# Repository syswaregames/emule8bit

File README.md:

# emule8bit
Emule - NES Emulator, 8-bit architecture, 6500 processor 
Optimized for MACOSX

8-bits
Binary: 11111111 (FF)

The only requirement is having X11 installed. X11 is no longer included in macOS, but X11 server and client libraries are available from the XQuartz project (see https://support.apple.com/en-us/HT201341).

You can download X11 from https://www.xquartz.org/ and easily install it. Typical installation path is /usr/X11 and it contains includes and libraries for X11 and OpenGL.

16kb Chunks = ROM -> Cpu maps reads

PPU

 -> Patern Memory "CHR ROM" 8kb 0x0000 - 0x1FFF (Sprites)
   -> Name Table Memory "VRAM" 2kb 0x2000 - 0x3EFF (Layout of Background)
    -> Palett Memory 0xF00 - 0x3FFF (decide which colors are displayed on the screen )

  Tile is 8 * 8 bitmap, 2 bits per pixel, (16bytes) four colors per pixel

    // Characters on NES
	// ~~~~~~~~~~~~~~~~~
	// The NES stores characters using 2-bit pixels. These are not stored sequentially
	// but in singular bit planes. For example:
	//
 	// 2-Bit Pixels       LSB Bit Plane     MSB Bit Plane
	// 0 0 0 0 0 0 0 0	  0 0 0 0 0 0 0 0   0 0 0 0 0 0 0 0
	// 0 1 1 0 0 1 1 0	  0 1 1 0 0 1 1 0   0 0 0 0 0 0 0 0
	// 0 1 2 0 0 2 1 0	  0 1 1 0 0 1 1 0   0 0 1 0 0 1 0 0
	// 0 0 0 0 0 0 0 0 =  0 0 0 0 0 0 0 0 + 0 0 0 0 0 0 0 0
	// 0 1 1 0 0 1 1 0	  0 1 1 0 0 1 1 0   0 0 0 0 0 0 0 0
	// 0 0 1 1 1 1 0 0	  0 0 1 1 1 1 0 0   0 0 0 0 0 0 0 0
	// 0 0 0 2 2 0 0 0	  0 0 0 1 1 0 0 0   0 0 0 1 1 0 0 0
	// 0 0 0 0 0 0 0 0	  0 0 0 0 0 0 0 0   0 0 0 0 0 0 0 0
	//
	// The planes are stored as 8 bytes of LSB, followed by 8 bytes of MSB

PPU - Palett

The NES PPU uses a background palette with up to 13 of these colors at a time, consisting of one common backdrop color and four subpalettes of three colors, chosen from the above set. The PPU's video memory layout allows choosing one subpalette for each 16×16 pixel area of the background. (A special video mode of the MMC5 mapper overrides this, assigning a subpalette to each 8×8-pixel tile.) Sprites have an additional set of four 3-color subpalettes (with color 0 being transparent in each) and every 8x8 or 8x16 pixels can have their own subpalette, allowing for a total of 12 different colors to use for sprites at any given time, or a total of 25 on-screen colors.

Because of the constraints mentioned above, converting a photograph often results in attribute clash at 16×16-pixel boundaries. Conversions with and without dithering follow, using the hex palette 0F160608 0F162720 0F090010 0F0A1910 (the repeated 0F represents black as the common backdrop color).

NES Resolution 256 -> X  Pixels
                ^
                | 240 Y

8-bit graphics refers to the capability of every pixel to use 8 bits for storing the amount of colors that can be displayed. In a nutshell, 8-bit graphics refers to maximum 256 colors that can be displayed, whereas 16 bit means 65,536 colors and 34 bit means 16,777,215 colors.

Color-wise, the NES used a palette of 56 colors across the board for all games. Rather than being mathematically created by 2-bit RGB values (like the Sega Master System's 64 color palette), instead the NES's palette seems to have been hand-selected and is a bit different.

How many colors did NES sprites have? 4 colors
Number of Colors Per Sprite
Sprites on the NES were limited to 4 colors (or 3 colors + transparency)

original 1985 Front-Loading NES motherboard.
https://github.com/Redherring32/OpenTendo

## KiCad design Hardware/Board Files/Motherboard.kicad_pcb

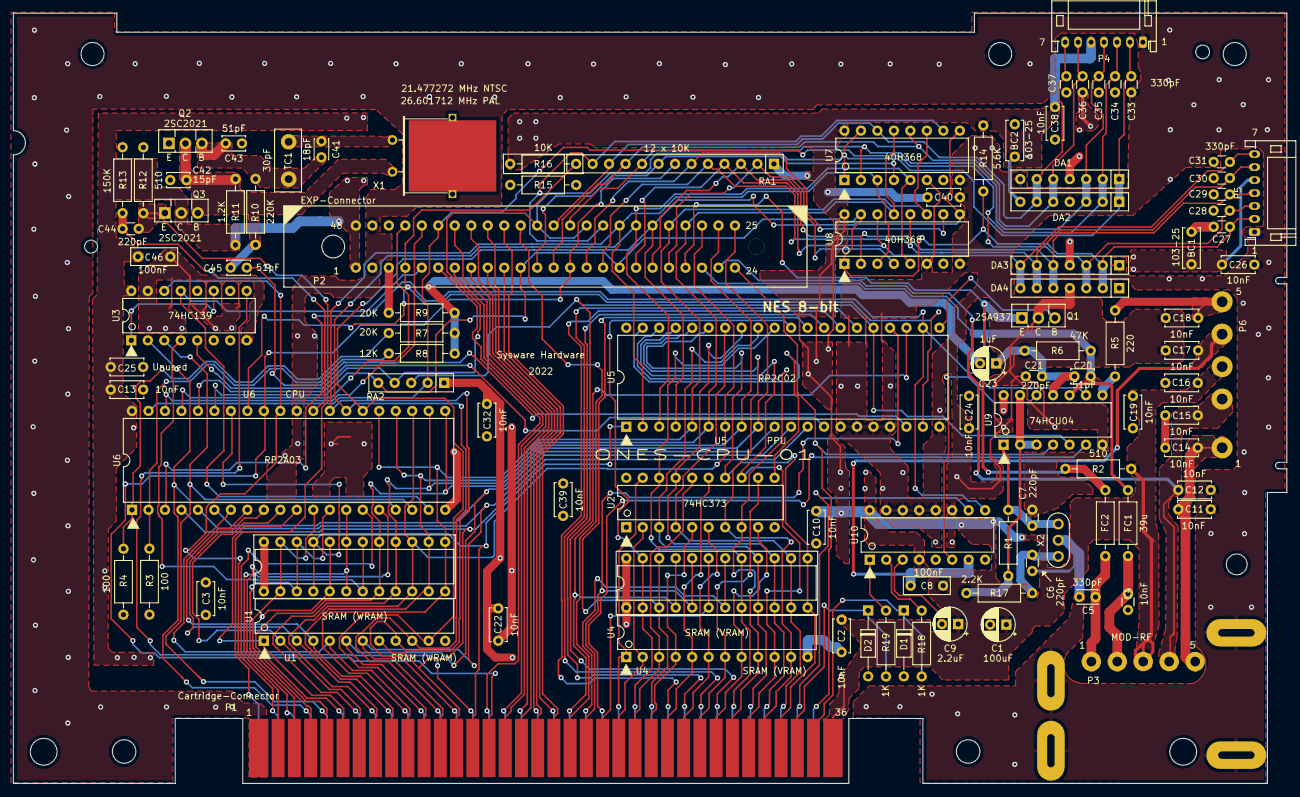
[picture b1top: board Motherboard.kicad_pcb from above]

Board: 2 copper layers, 196.3 x 118.7 mm, 101 parts (0 on the bottom side), 119 nets.

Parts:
 : DIP-24_W7.62mmSingleRow
 #2: DIP-24_W7.62mmSingleRow
BC1, BC2: 103-25; C_Disc_D6.0mm_W2.5mm_P5.00mm
C1: 100uF; CP_Radial_D5.0mm_P2.50mm
C2, C3, C10, C11, C12, C13, C14, C15, C16, C17, C18, C19, C22, C24, C26, C32, C38, C39, C40: 10nF; C_Disc_D5.0mm_W2.5mm_P5.00mm
C4: 10nF; C_Disc_D3.0mm_W1.6mm_P2.50mm
C5: 330pF; C_Disc_D3.0mm_W2.0mm_P2.50mm
C6, C7, C21, C44: 220pF; C_Disc_D3.0mm_W1.6mm_P2.50mm
C8, C46: 100nF; C_Disc_D7.0mm_W2.5mm_P5.00mm
C9: 2.2uF; CP_Radial_D5.0mm_P2.50mm
C20, C43, C45: 51pF; C_Disc_D3.4mm_W2.1mm_P2.50mm
C23: 1uF; CP_Radial_D5.0mm_P2.50mm
C25: (Unused); C_Disc_D5.0mm_W2.5mm_P5.00mm
C27, C28, C29, C30, C31, C33, C34, C35, C36, C37: 330pF; C_Disc_D3.0mm_W1.6mm_P2.50mm
C41: 18pF; C_Disc_D3.0mm_W2.0mm_P2.50mm
C42: 15pF; C_Disc_D3.4mm_W2.1mm_P2.50mm
D1, D2: ?; D_DO-35_SOD27_P10.16mm_Horizontal
DA1, DA3: DAN601; R_Array_SIP7
DA2, DA4: UPA64H; R_Array_SIP7
FC1: 39u; R_Axial_DIN0207_L6.3mm_D2.5mm_P10.16mm_Horizontal
FC2: Ferrite_Coil; R_Axial_DIN0207_L6.3mm_D2.5mm_P10.16mm_Horizontal
P1: 72-Pin Connector; NES_Edge_Connector
P2: EXP-Connector; EXP_Header
P3: MOD RF; Mod_RF
P4, P5: Controller Input; JST_PH_S7B-PH-K_1x07_P2.00mm_Horizontal
P6: PWR/RST IN; PowerReset-switch-In
Q1: 2SA937; TO-126-3_Vertical
Q2, Q3: 2SC2021; TO-126-3_Vertical
R1: 1M; R_Axial_DIN0207_L6.3mm_D2.5mm_P10.16mm_Horizontal
R2, R12: 510; R_Axial_DIN0207_L6.3mm_D2.5mm_P10.16mm_Horizontal
R3, R4: 100; R_Axial_DIN0207_L6.3mm_D2.5mm_P10.16mm_Horizontal
R5: 220; R_Axial_DIN0207_L6.3mm_D2.5mm_P10.16mm_Horizontal
R6: 47K; R_Axial_DIN0207_L6.3mm_D2.5mm_P10.16mm_Horizontal
R7, R9: 20K; R_Axial_DIN0207_L6.3mm_D2.5mm_P10.16mm_Horizontal
R8: 12K; R_Axial_DIN0207_L6.3mm_D2.5mm_P10.16mm_Horizontal
R10: 220K; R_Axial_DIN0207_L6.3mm_D2.5mm_P10.16mm_Horizontal
R11: 1.2K; R_Axial_DIN0207_L6.3mm_D2.5mm_P10.16mm_Horizontal
R13: 150K; R_Axial_DIN0207_L6.3mm_D2.5mm_P10.16mm_Horizontal
R14: 5.6K; R_Axial_DIN0207_L6.3mm_D2.5mm_P10.16mm_Horizontal
R15: R15; R_Axial_DIN0207_L6.3mm_D2.5mm_P10.16mm_Horizontal
R16: 10K; R_Axial_DIN0207_L6.3mm_D2.5mm_P10.16mm_Horizontal_OverLappi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
R17: 2.2K; R_Axial_DIN0207_L6.3mm_D2.5mm_P10.16mm_Horizontal
R18, R19: 1K; R_Axial_DIN0207_L6.3mm_D2.5mm_P10.16mm_Horizontal
RA1: 12 x 10K; R_Array_SIP13
RA2: 4 x 6.8K; R_Array_SIP5
TC1: 30pF; TrimmerCap-THT
U1: 6116 (WRAM); DIP-24_W7.62mm
U2: 74HC373; DIP-20_W7.62mm
U3: 74HC139; DIP-16_W7.62mm
U4: 6116 (VRAM); DIP-24_W7.62mm
U5: RP2C02 PPU; DIP-40_W15.24mm
U6: RP2A03 CPU; DIP-40_W15.24mm
U7: 40H368 (CI); DIP-16_W7.62mm
U8: 40H368 (CII); DIP-16_W7.62mm
U9: 74LS04; DIP-14_W7.62mm
U10: CIC; DIP-16_W7.62mm
X1: 21.477272 MHz; Crystal_HC49-U_Horizontal_1EP_style2
X2: 4MHz; Resonator_muRata_CSTLSxxxG-3Pin_W8.0mm_H3.0mm

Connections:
/4016-D0: C35.1, DA1.3, DA2.3, P2.35, P4.4, RA1.9, U7.2
/4016-D1: P2.12, RA1.8, U7.4
/4016-D2: P2.33, RA1.12, U7.10
/4016-D3: C36.1, DA1.5, DA2.5, P2.13, P4.6, RA1.10, U7.12
/4016-D4: C37.1, DA1.6, DA2.6, P2.36, P4.7, RA1.11, U7.14
/4017-D0: C29.1, DA3.5, DA4.5, P2.19, P5.4, RA1.3, U8.2
/4017-D1: P2.20, RA1.2, U8.4
/4017-D2: P2.15, RA1.6, U8.10
/4017-D3: C30.1, DA3.6, DA4.6, P2.16, P5.6, RA1.5, U8.12
/4017-D4: C31.1, DA3.7, DA4.7, P2.18, P5.7, RA1.4, U8.14
/+9V: C12.2, C15.2, P2.23, P3.4, P6.2
/ALE: U2.11, U5.39
/AUDIO: C4.2, P3.2
/CIC-CLK: P1.71, P2.24, U9.4
/CIC-RST: P1.70, U10.10
/CIC-TO-CART: D2.1, P1.34, R19.1
/CIC-TO-MB: D1.1, P1.35, R18.1
/CPU-A0: P1.13, U1.8, U5.12, U6.4
/CPU-A1: P1.12, U1.7, U5.11, U6.5
/CPU-A2: P1.11, U1.6, U5.10, U6.6
/CPU-A3: P1.10, U1.5, U6.7
/CPU-A4: P1.9, U1.4, U6.8
/CPU-A5: P1.8, U1.3, U6.9
/CPU-A6: P1.7, U1.2, U6.10
/CPU-A7: P1.6, U1.1, U6.11
/CPU-A8: #2.23, P1.5, U1.23, U6.12
/CPU-A9: #2.22, P1.4, U1.22, U6.13
/CPU-A10: #2.19, P1.3, U1.19, U6.14
/CPU-A11: P1.2, U6.15
/CPU-A12: P1.39, U6.16
/CPU-A13: P1.40, U3.2, U6.17
/CPU-A14: P1.41, U3.3, U6.18
/CPU-A15: P2.5, U3.13, U6.19
/CPU-CLK: C44.2, R13.1, U6.29
/CPU-D0: P1.49, P2.32, U1.9, U5.2, U6.28, U7.3, U8.3
/CPU-D1: P1.48, P2.31, U1.10, U5.3, U6.27, U7.5, U8.5
/CPU-D2: P1.47, P2.30, U1.11, U5.4, U6.26, U7.9, U8.9
/CPU-D3: #2.13, P1.46, P2.29, U1.13, U5.5, U6.25, U7.11, U8.11
/CPU-D4: #2.14, P1.45, P2.28, U1.14, U5.6, U6.24, U7.13, U8.13
/CPU-D5: #2.15, P1.44, P2.27, U1.15, U5.7, U6.23
/CPU-D6: #2.16, P1.43, P2.26, U1.16, U5.8, U6.22
/CPU-D7: #2.17, P1.42, P2.25, U1.17, U5.9, U6.21
/CPU-R~W: #2.21, P1.14, U1.21, U5.1, U6.34
/EXP-0: P1.16, P2.42
/EXP-1: P1.17, P2.41
/EXP-2: P1.18, P2.40
/EXP-3: P1.19, P2.39
/EXP-4: P1.20, P2.38
/EXP-5: P1.55, P2.10
/EXP-7: P1.53, P2.8
/EXP-8: P1.52, P2.7
/EXP-9: P1.51, P2.6
/EXP-AUDIO-IN: P2.3, R9.1
/EXP-AUDIO-OUT: C20.2, P2.22, R6.2, U9.10
/EXP-VIDEO: FC2.1, P2.21, Q1.1, R2.2
/GND: #2.20, BC1.1, BC2.1, C1.2, C2.1, C3.1, C4.1, C5.2, C6.1, C7.1, C10.1, C11.1, C12.1, C13.1, C14.1, C15.1, C16.1, C17.1, C18.1, C19.1, C21.1, C22.1, C24.1, C25.1, C26.1, C27.2, C28.2, C29.2, C30.2, C31.2, C32.1, C33.2, C34.2, C35.2, C36.2, C37.2, C38.1, C39.1, C40.1, C42.1, C43.1, C46.1, D1.2, D2.2, DA1.7, DA2.4, DA3.1, DA4.4, P1.1, P1.72, P2.2, P2.47, P3.6, P4.1, P5.1, Q1.2, Q2.1, R3.1, R4.1, R12.2, R13.2, U1.12, U1.20, U2.1, U2.10, U3.8, U3.15, U4.12, U5.14, U5.15, U5.16, U5.17, U5.20, U6.20, U6.30, U7.6, U7.8, U8.6, U8.8, U9.7, U10.8, U10.11, U10.12, U10.13, U10.14, U10.15, X2.2
/M2: P1.38, U3.14, U6.31
/OUT-0: C28.1, C34.1, DA1.2, DA2.2, DA3.3, DA4.3, P2.43, P4.3, P5.3, RA2.2, U6.39
/OUT-1: P2.44, U6.38
/OUT-2: P2.45, U6.37
/PPU-A0: P1.29, U2.9, U4.8
/PPU-A1: P1.28, U2.12, U4.7
/PPU-A2: P1.27, U2.6, U4.6
/PPU-A3: P1.26, U2.15, U4.5
/PPU-A4: P1.25, U2.5, U4.4
/PPU-A5: P1.24, U2.16, U4.3
/PPU-A6: P1.23, U2.2, U4.2
/PPU-A7: P1.59, U2.19, U4.1
/PPU-A8: .23, P1.60, U4.23, U5.30
/PPU-A9: .22, P1.61, U4.22, U5.29
/PPU-A10: P1.63, U5.28
/PPU-A11: P1.62, U5.27
/PPU-A12: P1.64, U5.26
/PPU-A13: P1.65, RA2.3, U5.25, U9.5
/PPU-CLK: C45.2, U5.18
/PPU-D0: P1.30, U2.8, U4.9, U5.38
/PPU-D1: P1.31, U2.13, U4.10, U5.37
/PPU-D2: P1.32, U2.7, U4.11, U5.36
/PPU-D3: .13, P1.33, U2.14, U4.13, U5.35
/PPU-D4: .14, P1.69, U2.4, U4.14, U5.34
/PPU-D5: .15, P1.68, U2.17, U4.15, U5.33
/PPU-D6: .16, P1.67, U2.3, U4.16, U5.32
/PPU-D7: .17, P1.66, U2.18, U4.17, U5.31
/PPU-~A13: P1.58, U9.6
/PPU-~CE: U3.5, U5.13
/PPU-~RD: .20, P1.21, U4.20, U5.24
/PPU-~WE: .21, P1.56, U4.21, U5.23
/SOUND-1: R4.2, R7.1, U6.1
/SOUND-2: R3.2, R8.1, U6.2
/SYSTEM-CLK: C44.1, P1.37, Q3.1, R12.1
/VCC: .24, #2.24, BC1.2, BC2.2, C1.1, C2.2, C3.2, C8.1, C9.1, C10.2, C13.2, C16.2, C19.2, C22.2, C24.2, C25.2, C26.2, C32.2, C38.2, C39.2, C40.2, C46.2, DA1.4, DA2.7, DA3.4, DA4.1, P1.36, P2.1, P2.48, P3.3, P4.5, P5.5, P6.3, Q3.2, R2.1, R11.1, R14.1, R16.1, RA1.1, RA2.1, U1.24, U2.20, U3.16, U4.24, U5.40, U6.40, U7.16, U8.16, U9.14, U10.4, U10.16
/VIDEO: C5.1, FC2.2, P3.1
/VRAM-A10: .19, P1.22, U4.19
/VRAM-~CE: .18, P1.57, U4.18
/WRAM-~CE: #2.18, U1.18, U3.4
/~IRQ: P1.15, P2.14, RA1.7, U6.32
/~NMI: P2.4, RA1.13, U5.19, U6.33
/~OE1: C33.1, DA1.1, DA2.1, P2.34, P2.37, P4.2, RA2.4, U6.36, U7.1, U7.15
/~OE2: C27.1, DA3.2, DA4.2, P2.11, P2.17, P5.2, R14.2, RA2.5, U6.35, U8.1, U8.15
/~ROMSEL: P1.50, U3.9
/~RST: U5.22, U6.3, U9.9, U10.9
unnamed: C6.2, R17.2, X2.1
unnamed: C7.2, R1.2, U9.1, X2.3
unnamed: C9.2, U10.3
unnamed: C11.2, C14.2, P3.5, P6.1
unnamed: C8.2, C17.2, P6.4, U10.7
unnamed: C18.2, P6.5, R5.2
unnamed: C20.1, C21.2, C23.1, R6.1, U9.11
unnamed: C23.2, R7.2, R8.2, R9.2
unnamed: C41.1, TC1.2, X1.2
unnamed: C41.2, C43.2, Q2.3, R10.1, TC1.1
unnamed: C42.2, C45.1, Q2.2, Q3.3, R10.2, R11.2, X1.1
unnamed: Q1.3, U5.21
unnamed: R1.1, R17.1, U9.2, U9.3, U9.13
unnamed: R5.1, U9.8
unnamed: R18.2, U10.2
unnamed: R19.2, U10.1
unnamed: U3.1, U3.11
unnamed: U9.12, U10.6

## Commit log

2022-04-17 start project, processor 8-bit headers, x11 and XQuartz
2022-04-17 gitignore update
2022-04-17 Cartridge, Mapper, PPU implementation, but need to fix link error
2022-04-18 now its compile
2022-04-18 running snes test ROM
2022-04-18 Add printscreen
2022-04-18 Requirment
2022-04-18 compiler error, in progress, mapper
2022-04-18 compiler erros fixed
2022-04-18 PPU working and loading Sprites
2022-04-19 minor config
2022-04-20 PPU Foregrounds, in progress
2022-04-20 PPU clock full implementation
2022-04-20 Readme PPU more details
2022-04-20 hardware schematics
2022-04-20 roms
2022-04-22 README
